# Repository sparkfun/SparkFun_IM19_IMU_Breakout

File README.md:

SparkFun 9DoF IMU Breakout - IM19
========================================

[*SparkFun 9DoF IMU Breakout - IM19 (SEN-30381)*](https://www.sparkfun.com/sparkfun-9dof-imu-breakout-im19.html)

The Feyman (FMI) IM19 attitude module combines MEMS sensor data with GNSS RTK positioning data to provide high-precision attitude measurements. This enables advanced features, like tilt-compensated surveying and robust navigation through brief GNSS outages.

- **Survey-Grade Accuracy:** Delivers roll and pitch measurements accurate to within 0.05 degrees.
- **Tilt Compensation:** No more perfectly vertical survey poles! The IM19 can calculate a virtual digital level point at any tilt angle, revolutionizing field data collection.
- **Sensor Fusion:** Offers a continuous navigation solution (Dead Reckoning) even during brief GNSS signal loss, making it ideal for urban or obstructed environments.

When fed with NMEA **`GGA`**, **`GST`**, and **`RMC`** messages at **5Hz**, and a standard **Pulse-Per-Second timing signal**, the IM19 attitude module will output a proprietary NMEA ASCII `GPFMI` message which contains the compensated position of the tip of your surveying pole, plus the Roll, Pitch and Yaw of the IMU itself.

Our Breakout provides access to all three IM19 UART interfaces. `UART1` and `UART2` are accessible via a CH342 dual-channel USB-UART interface. `UART3` is accessible via a 4-pin locking JST connector. All three UARTs can be accessed via breadboard-compatible breakout pads too. The CH342 can be disconnected by simply pulling the `CH342_EN` breakout pad low; allowing full access to `UART1` and `UART2` via the breakout pads.

Power can be provided by USB, or the `VIN` (5V nominal) breakout pad. With care, you can also connect an external 3.3V supply to the `3V3` breakout pads or `Pin 1` of the JST connector. A jumper allows JST `Pin 1` to be configured for 5V input / output.

The IM19 attitude module is centered on the center of the PCB, simplifying your LEVER_ARM calculations. There is no X,Y offset to consider. The Z origin is 1.6mm above the top surface of the PCB (inside the IM19 module package); 3.2mm above the bottom surface of the PCB.

The 1.7" x 1.7" PCB is the same size as some of our RTK GNSS Boards, making it easy to stack the IM19 above or below your existing GNSS breakout board.

> [!NOTE]
> The IM19 needs to be fed with GNSS positioning data with a RTK Fixed solution *(RTK Fix)* in order to work correctly. This board will not work with non-RTK GNSS receivers.

Documentation
-------------

- **[Hookup Guide (docusaurus)](http://docs.sparkfun.com/SparkFun_IM19_IMU_Breakout/)** - A hookup guide for the SparkFun IM19 IMU breakout board hosted by GitHub pages.<br>

Repository Contents
-------------------

- **[/docs](/docs/)** - Online documentation files
	- [/assets](/docs/assets/) - Assets files
		- [/3d_model](/docs/assets/3d_model/) - 3D models for the board
		- [/board_files](/docs/assets/board_files/) - Design files for the board
			- [KiCad Design Files](/docs/assets/board_files/kicad_files.zip) (.zip)
			- [Schematic](/docs/assets/board_files/schematic.pdf) (.pdf)
			- [Dimensions](/docs/assets/board_files/dimensions.pdf) (.pdf)
		- [/component_documentation](/docs/assets/component_documentation/) - Datasheets for hardware components
		- [/img/hookup_guide](/docs/assets/img/hookup_guide/) - Images for hookup guide documentation - Hookup guide images for the board
		- /Hardware - Hardware design files (.brd, .sch)
			- /Production - Production files

Product Variants
----------------

- [SEN-30381](https://www.sparkfun.com/sparkfun-9dof-imu-breakout-im19.html) - IM19 IMU Breakout

Version History
---------------

- [v10](https://github.com/sparkfun/SparkFun_IM19_IMU_Breakout/releases/tag/v10) - Initial Release

License Information
-------------------

This product is ***open source***!

Please review the [`LICENSE.md`](./LICENSE.md) file for license information.

If you have any questions or concerns about licensing, please contact technical support on our [SparkFun forums](https://community.sparkfun.com/).

Distributed as-is; no warranty is given.

- Your friends at SparkFun.

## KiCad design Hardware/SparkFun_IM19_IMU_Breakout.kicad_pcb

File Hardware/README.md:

SparkFun <PRODUCT NAME> Design Files
=====================================

The .kicad_sch and .kicad_pcb files here are KiCad schematic and PCB design files from SparkFun Electronics.
KiCad can be found [here](https://www.kicad.org/).

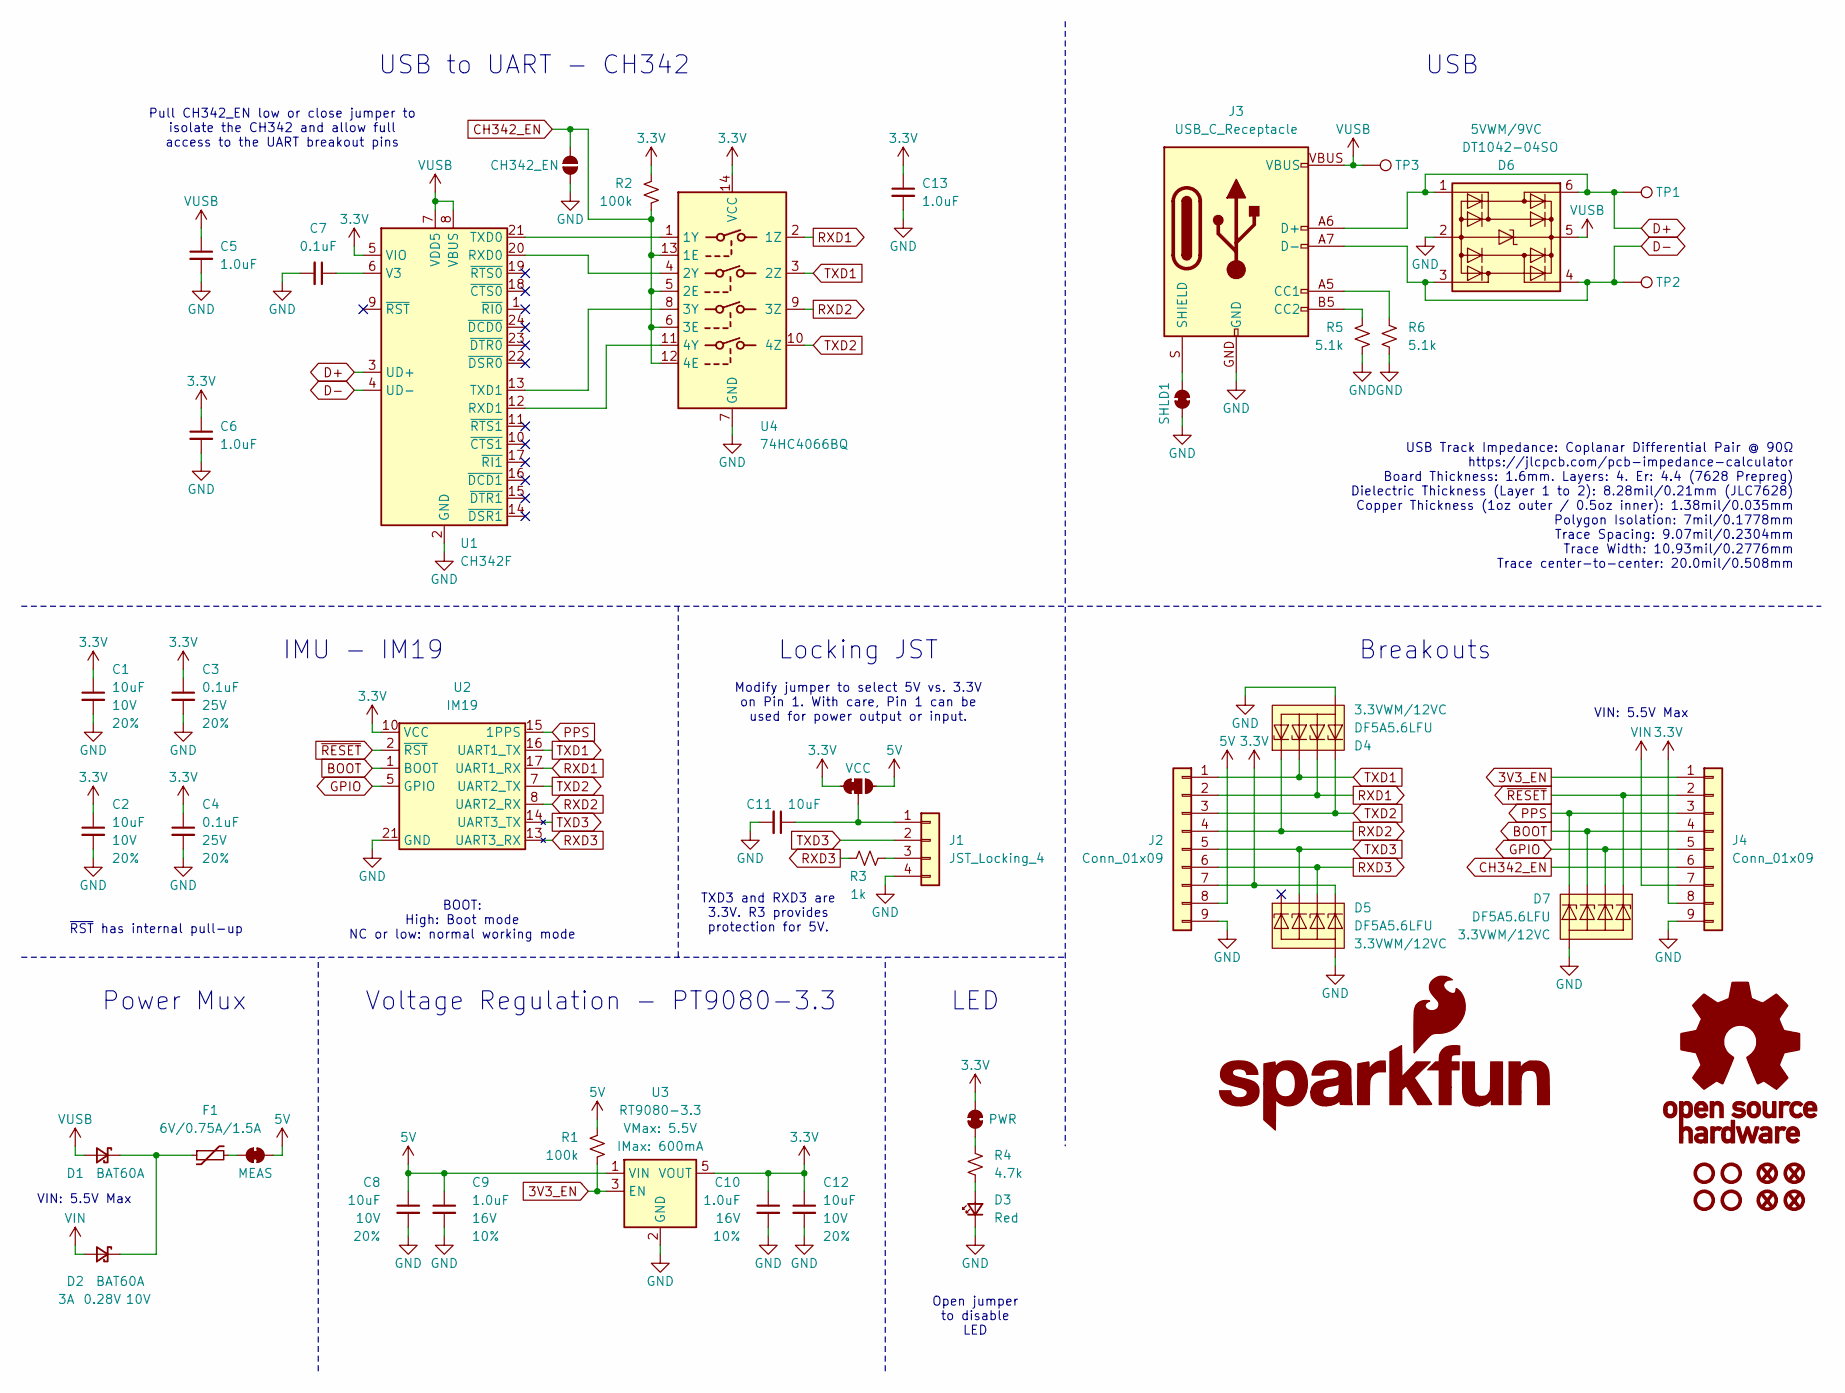
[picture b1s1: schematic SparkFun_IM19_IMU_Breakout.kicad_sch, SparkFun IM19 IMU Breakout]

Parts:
C1, C2, C8, C11, C12: 10uF; C_0603_1608Metric; Voltage 10V; Tolerance 20%
C3, C4, C7: 0.1uF; C_0603_1608Metric; Voltage 25V; Tolerance 20%
C5, C6, C9, C10, C13: 1.0uF; C_0603_1608Metric; Voltage 16V; Tolerance 10%
CH342_EN.1: CH342_EN; Jumper_2_NO
D1, D2: BAT60A; SOD-323
D3: Red; LED_0603_1608Metric_Red
D4, D5, D7: DF5A5.6LFU; SOT-353; Rating 3.3VWM/12VC
D6: DT1042-04SO; SOT23-6; Rating 5VWM/9VC
F1: 6V/0.75A/1.5A; 1206
FID1, FID2, FID3, FID4: Fiducial_0.5mm; Fiducial_0.5mm_Mask1mm
G1: SparkFun_Logo
G2: OSHW_Logo; Creative_Commons_License
J1: JST_Locking_4; JST_1x04_P1.25mm_Locking_Horizontal_SMD
J2, J4: Conn_01x09; 1x09_P2.54mm
J3: USB_C_Receptacle; USB-C_16
JP1: MEAS; Jumper_2_PTH_SMD_Combo-NC
PWR.1: PWR; Jumper_2_NC_Trace
R1, R2: 100k; R_0603_1608Metric
R3: 1k; R_0603_1608Metric
R4: 4.7k; R_0603_1608Metric
R5, R6: 5.1k; R_0603_1608Metric
SHLD1: Jumper_2_NC_Trace
ST1, ST2, ST3, ST4: Standoff
TP1, TP2, TP3: 1.25mm; TestPoint-1.25mm
U1: CH342F; QFN-24-1EP_4x4mm_P0.5mm_EP2.7x2.7mm
U2: IM19
U3: RT9080-3.3; SOT23-5
U4: 74HC4066BQ; QFN-14_2.5x3mm_P0.5mm_EP1x1.5mm
VCC.1: VCC; Jumper_3_NC-1_Trace

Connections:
3.3V: C1.1, C2.1, C3.1, C4.1, C6.1, C10.1, C12.1, C13.1, D5.5 (K4), J2.7, J4.8, PWR.1.2 (B), R2.2, U1.5 (VIO), U2.6 (VCC), U2.10 (VCC), U3.5 (VOUT), U4.14 (VCC), VCC.1.1 (A)
3V3_EN: J4.1, R1.1, U3.3 (EN)
5V: C8.1, C9.1, J2.8, JP1.2 (B), R1.2, U3.1 (VIN), VCC.1.3 (C)
BOOT: D7.4 (K3), J4.4, U2.1 (BOOT)
CH342_EN: CH342_EN.1.2 (B), J4.6, R2.1, U4.5 (2E), U4.6 (3E), U4.12 (4E), U4.13 (1E)
D+: D6.1 (I/O1), D6.6 (I/O4), J3.A6 (D+), J3.B6 (D+), TP1.1, U1.3 (UD+)
D-: D6.3 (I/O2), D6.4 (I/O3), J3.A7 (D-), J3.B7 (D-), TP2.1, U1.4 (UD-)
GND: C1.2, C2.2, C3.2, C4.2, C5.2, C6.2, C7.2, C8.2, C9.2, C10.2, C11.2, C12.2, C13.2, CH342_EN.1.1 (A), D3.1 (K), D4.2 (A), D5.2 (A), D6.2 (GND), D7.2 (A), J1.4, J2.9, J3.GND, J4.9, R5.1, R6.1, SHLD1.1 (A), U1.2 (GND), U1.25 (GND), U2.3 (GND), U2.4 (GND), U2.9 (GND), U2.18 (GND), U2.21 (GND), U3.2 (GND), U4.7 (GND)
GPIO: D7.3 (K2), J4.5, U2.5 (GPIO)
unnamed: D1.1 (K), D2.1 (K), F1.1
unnamed: D3.2 (A), R4.1
unnamed: C11.1, J1.1, VCC.1.2 (B)
unnamed: J1.3, R3.2
unnamed: J3.A5 (CC1), R6.2
unnamed: J3.B5 (CC2), R5.2
unnamed: J3.S (SHIELD), SHLD1.2 (B)
unnamed: F1.2, JP1.1 (A)
unnamed: PWR.1.1 (A), R4.2
unnamed: U1.20 (RXD0), U4.4 (2Y)
unnamed: U1.12 (RXD1), U4.11 (4Y)
unnamed: U1.21 (TXD0), U4.1 (1Y)
unnamed: U1.13 (TXD1), U4.8 (3Y)
unnamed: C7.1, U1.6 (V3)
PPS: D7.5 (K4), J4.3, U2.15 (1PPS)
RXD1: D4.4 (K3), J2.2, U2.17 (UART1_RX), U4.2 (1Z)
RXD2: D4.1 (K1), J2.4, U2.8 (UART2_RX), U4.9 (3Z)
RXD3: D5.4 (K3), J2.6, R3.1, U2.13 (UART3_RX)
TXD1: D4.3 (K2), J2.1, U2.16 (UART1_TX), U4.3 (2Z)
TXD2: D4.5 (K4), J2.3, U2.7 (UART2_TX), U4.10 (4Z)
TXD3: D5.3 (K2), J1.2, J2.5, U2.14 (UART3_TX)
VIN: D2.2 (A), J4.7
VUSB: C5.1, D1.2 (A), D6.5 (VCC), J3.VBUS, TP3.1, U1.7 (VDD5), U1.8 (VBUS)
~RESET: D7.1 (K1), J4.2, U2.2 (~RST)

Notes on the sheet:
Modify jumper to select 5V vs. 3.3V on Pin 1. With care, Pin 1 can be used for power output or input.
Power Mux
BOOT: High: Boot mode NC or low: normal working mode
IMU - IM19
USB
Breakouts
TXD3 and RXD3 are 3.3V. R3 provides protection for 5V.
USB to UART - CH342
Pull CH342_EN low or close jumper to isolate the CH342 and allow full access to the UART breakout pins
Voltage Regulation - PT9080-3.3
~{RST} has internal pull-up
USB Track Impedance: Coplanar Differential Pair @ 90Ω https://jlcpcb.com/pcb-impedance-calculator Board Thickness: 1.6mm. Layers: 4. Er: 4.4 (7628 Prepreg) Dielectric Thickness (Layer 1 to 2): 8.28mil/0.21mm (JLC7628) Copper Thickness (1oz outer / 0.5oz inner): 1.38mil/0.035mm Polygon Isolation: 7m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
Open jumper to disable LED
Locking JST
LED
VIN: 5.5V Max

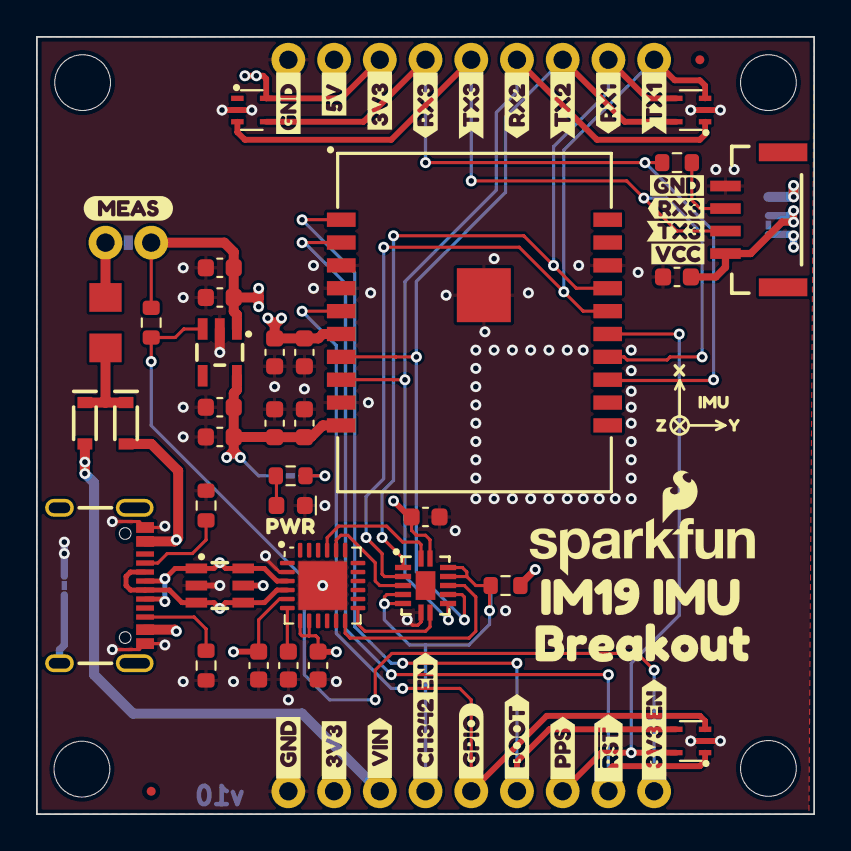
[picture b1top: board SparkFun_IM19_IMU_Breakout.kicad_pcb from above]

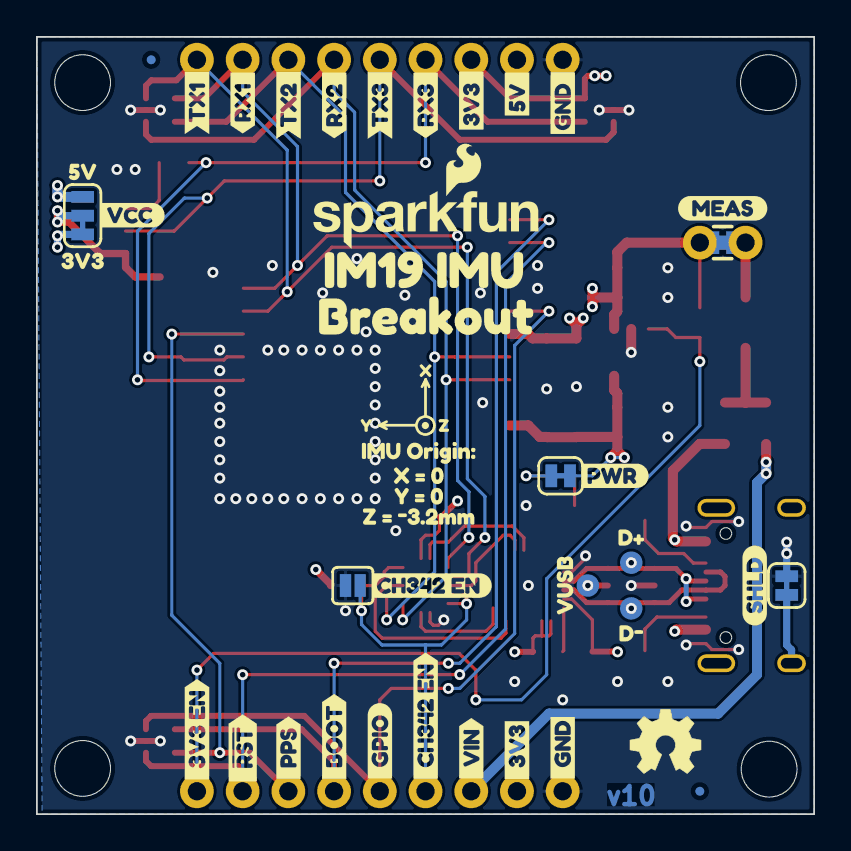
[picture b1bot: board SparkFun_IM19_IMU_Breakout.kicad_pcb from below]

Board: 4 copper layers, 43.2 x 43.2 mm, 120 parts (48 on the bottom side), 33 nets.

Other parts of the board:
Ref**: Val**; OSHW_Logo_4mm
kibuzzard-67FFA928: G***; kibuzzard-67FFA928
kibuzzard-67FFB45E, kibuzzard-67FFB45E#2: G***; kibuzzard-67FFB45E
kibuzzard-67FFB46A, kibuzzard-67FFB46A#2: G***; kibuzzard-67FFB46A
kibuzzard-67FFB450, kibuzzard-67FFB450#2: G***; kibuzzard-67FFB450
kibuzzard-68F5D5EE, kibuzzard-68F5D5EE#2: G***; kibuzzard-68F5D5EE
kibuzzard-68F5D6B2, kibuzzard-68F5D6B2#2: G***; kibuzzard-68F5D6B2
kibuzzard-68F5D6C3, kibuzzard-68F5D6C3#2: G***; kibuzzard-68F5D6C3
kibuzzard-68F5D6DA, kibuzzard-68F5D6DA#2: G***; kibuzzard-68F5D6DA
kibuzzard-68F5D9B9: G***; kibuzzard-68F5D9B9
kibuzzard-68F5D9CC: G***; kibuzzard-68F5D9CC
kibuzzard-68F5D9E8: G***; kibuzzard-68F5D9E8
kibuzzard-68F5D71D, kibuzzard-68F5D71D#2: G***; kibuzzard-68F5D71D
kibuzzard-68F5D97A: G***; kibuzzard-68F5D97A
kibuzzard-68F5D651, kibuzzard-68F5D651#2: G***; kibuzzard-68F5D651
kibuzzard-68F5D664, kibuzzard-68F5D664#2: G***; kibuzzard-68F5D664
kibuzzard-68F5D677, kibuzzard-68F5D677#2: G***; kibuzzard-68F5D677
kibuzzard-68F5D706, kibuzzard-68F5D706#2: G***; kibuzzard-68F5D706
kibuzzard-68F5DA6F, kibuzzard-68F5DA6F#2: G***; kibuzzard-68F5DA6F
kibuzzard-68F5DABB, kibuzzard-68F5DABB#2: G***; kibuzzard-68F5DABB
kibuzzard-68F5DAD8, kibuzzard-68F5DAD8#2: G***; kibuzzard-68F5DAD8
kibuzzard-68F5DB0E, kibuzzard-68F5DB0E#2: G***; kibuzzard-68F5DB0E
kibuzzard-68F5DB1B: G***; kibuzzard-68F5DB1B
kibuzzard-68F5DB2C, kibuzzard-68F5DB2C#2: G***; kibuzzard-68F5DB2C
kibuzzard-68F5DB3E, kibuzzard-68F5DB3E#2: G***; kibuzzard-68F5DB3E
kibuzzard-68F5DB51, kibuzzard-68F5DB51#2: G***; kibuzzard-68F5DB51
kibuzzard-68F5DB62, kibuzzard-68F5DB62#2: G***; kibuzzard-68F5DB62
kibuzzard-68F5DDAB: G***; kibuzzard-68F5DDAB
kibuzzard-68F5DDD0: G***; kibuzzard-68F5DDD0
kibuzzard-68F5DDF5: G***; kibuzzard-68F5DDF5
kibuzzard-68F5DE2E: G***; kibuzzard-68F5DE2E
kibuzzard-68F5E0B5, kibuzzard-68F5E0B5#2: G***; kibuzzard-68F5E0B5
kibuzzard-68F5E8F0: G***; kibuzzard-68F5E8F0
kibuzzard-68F5E8FA: G***; kibuzzard-68F5E8FA
kibuzzard-68F5E9AB: G***; kibuzzard-68F5E9AB
kibuzzard-68F5E9C6: G***; kibuzzard-68F5E9C6
kibuzzard-68F5E9E3: G***; kibuzzard-68F5E9E3
kibuzzard-68F5E094, kibuzzard-68F5E094#2: G***; kibuzzard-68F5E094
kibuzzard-68F5E982: G***; kibuzzard-68F5E982
kibuzzard-68F5EA91, kibuzzard-68F5EA91#2: G***; kibuzzard-68F5EA91
kibuzzard-68F5EC7C: G***; kibuzzard-68F5EC7C
kibuzzard-68F5ECB4: G***; kibuzzard-68F5ECB4
kibuzzard-68F5ECF3: G***; kibuzzard-68F5ECF3
kibuzzard-68F5EDC8: G***; kibuzzard-68F5EDC8
kibuzzard-68F62121: G***; kibuzzard-68F62121

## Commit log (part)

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2025-10-17 Initial Hardware commit - WIP
2025-10-18 More WIP
2025-10-20 Add PWR LED and silk. Ignore -backups
2025-10-20 Routed
2025-10-20 Panelized - ready for review
2025-11-12 Updates after review
2025-11-12 Correct typo
2025-11-12 Rename Schematic
2026-04-08 Remove unused directories
2026-04-08 Update files
    Add product description and links
    Update license, contribution, and issue files
    Update gitignore
2026-04-08 Add hardware files
    Adds the board design files (schematic, KiCad files, etc.)
    Adds the component documentation (datasheets, manuals, etc.)
2026-04-08 Add icons
    Add assets for custom icons
2026-04-08 Add banner images
2026-04-09 Update markdown
    Add README files
    Update Markdown syntax
    - Consistent indentation, line separation between headings, heading styles, etc.
2026-04-09 Remove cache files
2026-04-09 Add Site Generator
    Add default framework for Docusaurus
2026-04-10 Update SIte Generator
    Update the configurations for site generator
    Add site favicon
2026-04-10 Update icons
2026-04-10 Fix name
2026-04-10 Add Docusaurus files
2026-04-13 Add docs content
    Add content for the hookup guide
2026-04-13 Enable Iconify icons
    Enable the use of the Iconify icons
2026-04-13 Add Algolia search bar
2026-04-13 Deploy to GitHub Pages
    Adds action to deploy documentation to GitHub pages
2026-04-13 Update node packages
2026-04-13 Update docusaurus.config.ts
    Add edit link
    Change configuration to throw broken links
2026-04-13 Fix working directory
2026-04-13 Fix links
2026-04-13 Add *.step file
    Add 3D model assets
2026-04-13 Fix SSG Errors
2026-04-13 Fix broken links
2026-04-13 Enable image zoom
    Adds image zoom-in plugin
    Removes file links from images
2026-04-13 Fix typos
2026-04-17 Update docs

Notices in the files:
parts and their libraries:
Released under the Creative Commons Attribution Share-Alike 4.0 License
https://creativecommons.org/licenses/by-sa/4.0
